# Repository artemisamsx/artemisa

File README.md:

# Artemisa MSX Computer System

This repository contains documentation and designs for a MSX computer that can be build using discrete components and original integrated circuits, codenamed Artemisa.

This is still work in progress, but you may find some specs and designs in this repository.

## Documentation

* [Artemisa User Manual](doc/user-manual/000-index.md).
* [Artemisa Service Manual](doc/service-manual/000-index.md).

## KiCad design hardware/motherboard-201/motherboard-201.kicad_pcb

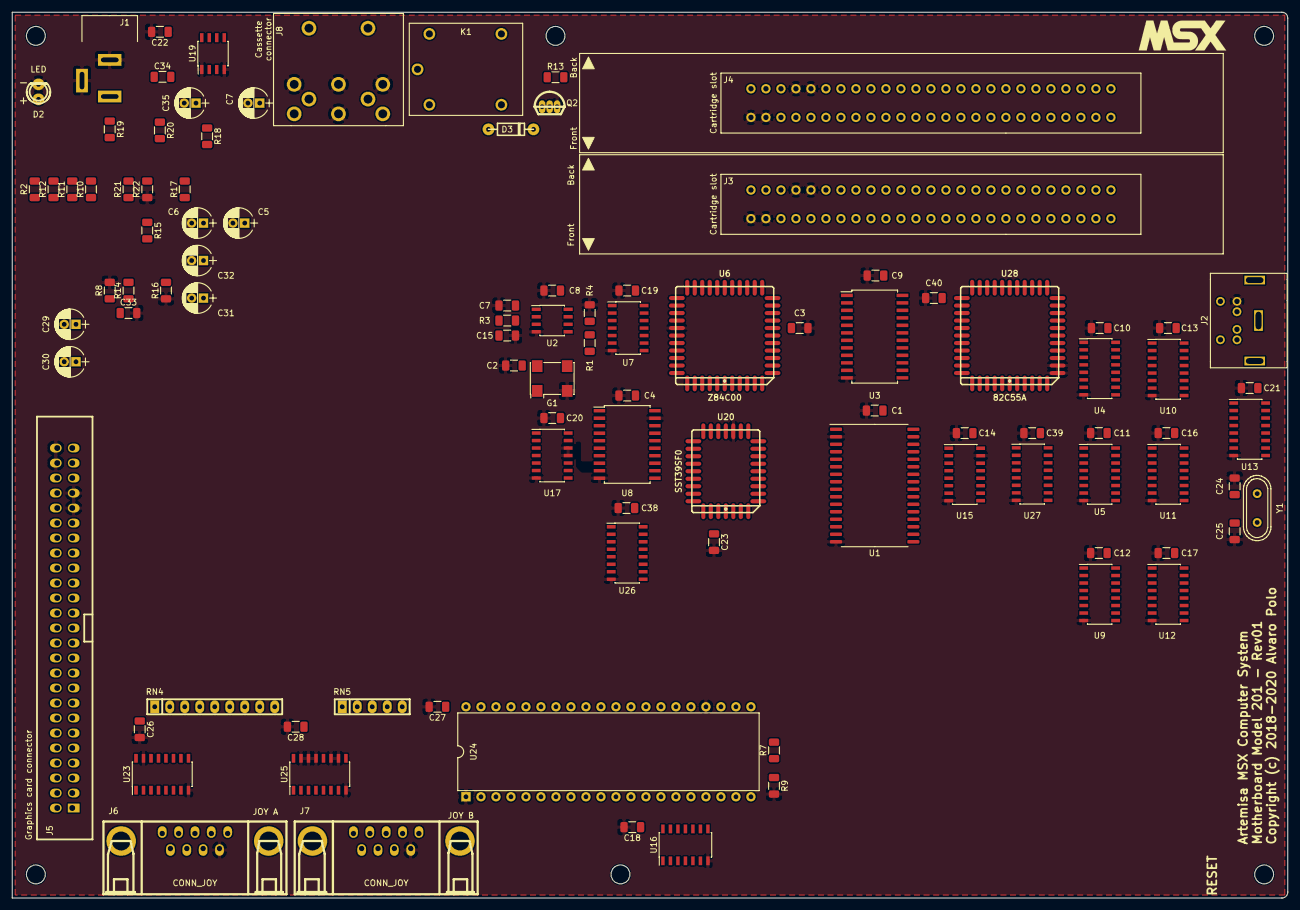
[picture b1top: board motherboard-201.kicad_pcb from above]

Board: 2 copper layers, 216.0 x 150.0 mm, 99 parts (0 on the bottom side), 158 nets, no tracks yet.

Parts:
C1, C2, C3, C4, C7, C8, C9, C14, C18, C19, C20, C22, C23, C26, C27, C28, C38, C39, C40: 100nF; C_1206
C5, C7#2: 100uF; Radial_capacitor
C6: 10uF; Radial_capacitor
C10, C11, C12, C13, C16, C17, C21: 0.1uF; C_1206
C15: 1uF; C_1206
C24, C25: 33pF; C_1206
C29, C30, C31: 10u; Radial_capacitor
C32, C35: 1uF; Radial_capacitor
C33, C34: 22nF; C_1206
D2: LED
D3: 1N4448; Axial_diode
G1: SG7050
J1: PWR_conn; Jack_55_21
J2: PS2_CONN; PS2_conn
J3, J4: MSX_Slot; Slot_conn
J5: GFX_Connector_Output; GFX_conn
J6, J7: CONN_JOY; Joystick_conn
J8: DIN8
K1: Relay
Q2: 2N2907; TO92
R1, R4, R7, R9: 10K; R_1206
R2: 220; R_1206
R3: 560; R_1206
R8: 470; R_1206
R10: 20k; R_1206
R11, R14, R15, R17: 4k7; R_1206
R12, R21, R22: 2k7; R_1206
R13: 2k2; R_1206
R16: 100; R_1206
R18: 220k; R_1206
R19: 1k; R_1206
R20: 10k; R_1206
RN4: 10K; RN8
RN5: 10K; RN4
U1: AS6C1008; SOP-32_450
U2: TL7705; SOIC-8_150
U3: GAL_declogic-201; SOIC-24
U4, U5, U9, U10, U11, U12: 74HC670; SOIC-16
U6: Z84C00; PLCC44
U7, U17: 74HC74; SOIC-14
U8: 74HCT245; SOIC-20
U13: ATMEGA328P; SOIC-16
U15: 74HC139; SOIC-16
U16: 74LS07; SOIC-14
U19: LM311; SOIC-8_150
U20: SST39SF0; PLCC32
U23, U25: 74HC157; SOIC-16
U24: AY-3-8910; DIP-40_600
U26: 74HC138; SOIC-16
U27: 74HC153; SOIC-16
U28: 82C55A; PLCC44
Y1: 16Mhz; Crystal

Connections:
/ADDR0: J3.28, J4.28, J5.28, U1.12, U3.9, U6.34, U20.12, U28.10
/ADDR1: J3.27, J4.27, J5.27, U1.11, U3.10, U6.35, U20.11, U28.9
/ADDR14: J3.25, J4.25, J5.25, U1.3, U3.11, U6.4, U20.29, U27.14
/ADDR15: J3.18, J4.18, J5.18, U1.31, U3.13, U6.5, U27.2
/AUDIO: J5.49, R10.2, R11.2, R12.2
/BEEP: C29.1, U28.11
/CASIN: R19.1, U19.7, U24.14
/CASOUT: C32.1, U28.14
/CLK: G1.3, J3.42, J4.42, J5.42, U6.7, U7.3, U7.11, U17.3
/CPU/ADDR2: J3.30, J4.30, J5.30, U1.10, U6.36, U20.10
/CPU/ADDR3: J3.29, J4.29, J5.29, U1.9, U6.37, U20.9, U26.1
/CPU/ADDR4: J3.32, J4.32, J5.32, U1.8, U6.38, U20.8, U26.2
/CPU/ADDR5: J3.31, J4.31, J5.31, U1.7, U6.39, U20.7, U26.3
/CPU/ADDR6: J3.22, J4.22, J5.22, U1.6, U6.40, U20.6, U26.5
/CPU/ADDR7: J3.21, J4.21, J5.21, U1.5, U6.41, U20.5, U26.6
/CPU/ADDR8: J3.24, J4.24, J5.24, U1.27, U6.42, U20.27
/CPU/ADDR9: J3.17, J4.17, J5.17, U1.26, U6.43, U20.26
/CPU/ADDR10: J3.20, J4.20, J5.20, U1.23, U6.44, U20.23
/CPU/ADDR11: J3.19, J4.19, J5.19, U1.25, U6.1, U20.25
/CPU/ADDR12: J3.23, J4.23, J5.23, U1.4, U6.2, U20.4
/CPU/ADDR13: J3.26, J4.26, J5.26, U1.28, U6.3, U20.28
/CPU/D0: U6.16, U8.2
/CPU/D1: U6.17, U8.3
/CPU/D2: U6.14, U8.4
/CPU/D3: U6.9, U8.5
/CPU/D4: U6.8, U8.6
/CPU/D5: U6.10, U8.7
/CPU/D6: U6.11, U8.8
/CPU/D7: U6.15, U8.9
/CPU/DATA0: J3.34, J4.34, J5.34, U1.13, U8.18, U20.13, U24.37, U28.38
/CPU/DATA1: J3.33, J4.33, J5.33, U1.14, U8.17, U20.14, U24.36, U28.37
/CPU/DATA2: J3.36, J4.36, J5.36, U1.15, U8.16, U20.15, U24.35, U28.36
/CPU/DATA3: J3.35, J4.35, J5.35, U1.17, U8.15, U20.17, U24.34, U28.35
/CPU/DATA4: J3.38, J4.38, J5.38, U1.18, U8.14, U20.18, U24.33, U28.33
/CPU/DATA5: J3.37, J4.37, J5.37, U1.19, U8.13, U20.19, U24.32, U28.32
/CPU/DATA6: J3.40, J4.40, J5.40, U1.20, U8.12, U20.20, U24.31, U28.31
/CPU/DATA7: J3.39, J4.39, J5.39, U1.21, U8.11, U20.21, U24.30, U28.30
/DATADIR: U3.14, U8.1
/DECODING/~IOSL: U3.20, U26.4
/DECODING/~PPISL: U3.7, U17.10, U26.10
/DECODING/~PSGSL: U3.8, U26.11
/EXTSOUND: C30.1, J3.49, J4.49
/KBD/D0: U4.15, U5.15, U9.15, U10.15, U11.15, U12.15
/KBD/D1: U4.1, U5.1, U9.1, U10.1, U11.1, U12.1
/KBD/D2: U4.2, U5.2, U9.2, U10.2, U11.2, U12.2
/KBD/D3: U4.3, U5.3, U9.3, U10.3, U11.3, U12.3
/KBD/KBCOL0: U4.10, U5.10, U9.10, U28.20
/KBD/KBCOL1: U4.9, U5.9, U9.9, U28.21
/KBD/KBCOL2: U4.7, U5.7, U9.7, U28.22
/KBD/KBCOL3: U4.6, U5.6, U9.6, U28.24
/KBD/KBCOL4: U10.10, U11.10, U12.10, U28.25
/KBD/KBCOL5: U10.9, U11.9, U12.9, U28.26
/KBD/KBCOL6: U10.7, U11.7, U12.7, U28.27
/KBD/KBCOL7: U10.6, U11.6, U12.6, U28.28
/KBD/KBROW0: U4.5, U5.5, U9.5, U10.5, U11.5, U12.5, U28.16
/KBD/KBROW1: U4.4, U5.4, U9.4, U10.4, U11.4, U12.4, U28.17
/KBD/KBROW2: U15.14, U28.18
/KBD/KBROW3: U15.13, U28.19
/KBD/ROW0: U4.14, U5.14, U9.14, U10.14, U11.14, U12.14
/KBD/ROW1: U4.13, U5.13, U9.13, U10.13, U11.13, U12.13
/KBD/~RSL0: U4.11, U10.11, U15.12
/KBD/~RSL1: U5.11, U11.11, U15.11
/KBD/~RSL2: U9.11, U12.11, U15.10
/KBD/~WSL0H: U10.12, U13.15
/KBD/~WSL0L: U4.12, U13.14
/KBD/~WSL1L: U5.12, U13.16
/PPI/PA0: U27.6, U28.5
/PPI/PA1: U27.10, U28.4
/PPI/PA2: U27.5, U28.3
/PPI/PA3: U27.11, U28.2
/PPI/PA4: U27.4, U28.44
/PPI/PA5: U27.12, U28.43
/PPI/PA6: U27.3, U28.42
/PPI/PA7: U27.13, U28.41
/PSG/IOA0: U23.4, U24.21
/PSG/IOA1: U23.7, U24.20
/PSG/IOA2: U23.9, U24.19
/PSG/IOA3: U23.12, U24.18
/PSG/IOA4: U24.17, U25.4
/PSG/IOA5: U24.16, U25.7
/PSG/IOB0: U16.1, U24.13
/PSG/IOB1: U16.3, U24.12
/PSG/IOB2: U16.5, U24.11
/PSG/IOB3: U16.9, U24.10
/PSG/IOB4: J6.8, U24.9
/PSG/IOB5: J7.8, U24.8
/PSG/IOB6: U23.1, U24.7, U25.1
/PSG/JOYA1: J6.1, RN4.9, U23.2
/PSG/JOYA2: J6.2, RN4.8, U23.5
/PSG/JOYA3: J6.3, RN4.7, U23.11
/PSG/JOYA4: J6.4, RN4.6, U23.14
/PSG/JOYA6: J6.6, RN5.5, U16.8, U25.2
/PSG/JOYA7: J6.7, RN5.4, U16.6, U25.5
/PSG/JOYB1: J7.1, RN4.5, U23.3
/PSG/JOYB2: J7.2, RN4.4, U23.6
/PSG/JOYB3: J7.3, RN4.3, U23.10
/PSG/JOYB4: J7.4, RN4.2, U23.13
/PSG/JOYB6: J7.6, RN5.3, U16.4, U25.3
/PSG/JOYB7: J7.7, RN5.2, U16.2, U25.6
/PSGBC1: U3.19, U24.29
/PSGBDIR: U3.18, U24.27
/PSGCLK: U17.5, U24.22
/RESET: R4.2, U2.6, U28.39
/~CAPSLOCK: U13.6, U28.13
/~CASMOTOR: R13.2, U28.15
/~CS1: J3.1, J4.1, J5.1, U3.21
/~CS2: J3.2, J4.2, J5.2, U3.22
/~CS12: J3.3, J4.3, J5.3, U3.23
/~INT: J3.8, J4.8, J5.8, U6.18
/~IORQ: J3.11, J4.11, J5.11, U3.4, U6.22
/~KANALOCK: R9.1, U13.11, U24.6
/~M1: J3.9, J4.9, J5.9, U3.5, U6.31, U7.2
/~MREQ: J3.12, J4.12, J5.12, U3.3, U6.21
/~PPIRD: U3.15, U28.6
/~PPIRDY: U17.8, U27.1, U27.15
/~PPIWR: U3.16, U28.40
/~RD: J3.14, J4.14, J5.14, U1.24, U3.1, U6.23, U20.24
/~RESET: J3.15, J4.15, J5.15, R1.2, U2.5, U6.30, U13.1, U17.13, U24.23
/~RFSH: J3.6, J4.6, J5.6, U3.6, U6.32
/~SLTSL0: U15.4, U20.22
/~SLTSL1: U1.22, U15.5
/~SLTSL2: J3.4, U15.6
/~SLTSL3: J4.4, U15.7
/~SLTSLEN: U3.17, U15.1
/~VDPSL: J5.16, U26.12
/~WAIT: J3.7, J4.7, J5.7, U7.1, U7.10
/~WR: J3.13, J4.13, J5.13, U1.29, U3.2, U6.26
GND: C1.2, C2.2, C3.2, C4.2, C5.2, C6.2, C7.2, C7#2.2, C8.1, C9.2, C10.1, C11.1, C12.1, C13.1, C14.2, C15.2, C16.1, C17.1, C18.2, C19.2, C20.2, C21.1, C22.2, C23.2, C24.1, C25.1, C26.2, C27.2, C28.2, C33.2, C35.2, C38.2, C39.2, C40.2, D2.2, G1.2, J1.2, J1.3, J2.3, J3.41, J3.43, J3.48, J3.50, J4.41, J4.43, J4.48, J4.50, J5.41, J5.43, J5.48, J5.50, J6.9, J7.9, J8.1, J8.2, J8.3, J8.8, Q2.1, R4.1, R8.2, R9.2, R16.1, R22.1, U1.2, U1.16, U2.4, U3.12, U4.8, U5.8, U6.33, U7.7, U8.10, U8.19, U9.8, U10.8, U11.8, U12.8, U13.8, U15.8, U15.15, U16.7, U17.7, U17.11, U17.12, U19.1, U19.4, U20.16, U23.8, U23.15, U24.1, U24.24, U25.8, U25.10, U25.11, U25.13, U25.14, U25.15, U26.8, U27.8, U28.7, U28.8
unnamed: C7.1, C7#2.1, U2.1
unnamed: C15.1, R3.2
unnamed: C24.2, U13.9, Y1.1
unnamed: C25.2, U13.10, Y1.2
unnamed: C29.2, R10.1
unnamed: C30.2, R11.1
unnamed: C31.1, R8.1, U24.3, U24.4, U24.38
unnamed: C31.2, R12.1
unnamed: C32.2, R14.2
unnamed: C33.1, R14.1, R15.2
unnamed: C34.1, R17.1
unnamed: C34.2, J8.5
unnamed: C35.1, R20.2, R21.1, R22.2, U19.2
unnamed: D2.1, R2.2
unnamed: D3.1, K1.2, Q2.3
unnamed: J2.1, U13.5
unnamed: J2.5, U13.4
unnamed: J8.4, R15.1, R16.2
unnamed: J8.6, K1.4
unnamed: J8.7, K1.3
unnamed: Q2.2, R13.1
unnamed: R3.1, U2.3
unnamed: R7.2, U24.15
unnamed: R17.2, R18.1, R20.1, U19.3
unnamed: U6.28, U7.5, U7.12
unnamed: U7.4, U7.9
unnamed: U15.2, U27.7
unnamed: U15.3, U27.9
unnamed: U17.2, U17.6
~: C1.1, C2.1, C3.1, C4.1, C5.1, C6.1, C8.2, C9.1, C10.2, C11.2, C12.2, C13.2, C14.1, C16.2, C17.2, C18.1, C19.1, C20.1, C21.2, C22.1, C23.1, C26.1, C27.1, C28.1, C38.1, C39.1, C40.1, D3.2, G1.1, G1.4, J1.1, J2.4, J3.45, J3.47, J4.45, J4.47, J5.4, J5.45, J5.47, J6.5, J7.5, K1.1, R1.1, R2.1, R7.1, R18.2, R19.2, R21.2, RN4.1, RN5.1, U1.30, U1.32, U2.2, U2.7, U2.8, U3.24, U4.16, U5.16, U6.13, U6.19, U6.29, U7.13, U7.14, U8.20, U9.16, U10.16, U11.16, U12.16, U13.7, U15.16, U16.14, U17.1, U17.4, U17.14, U19.8, U20.31, U20.32, U23.16, U24.25, U24.28, U24.40, U25.16, U26.16, U27.16, U28.29

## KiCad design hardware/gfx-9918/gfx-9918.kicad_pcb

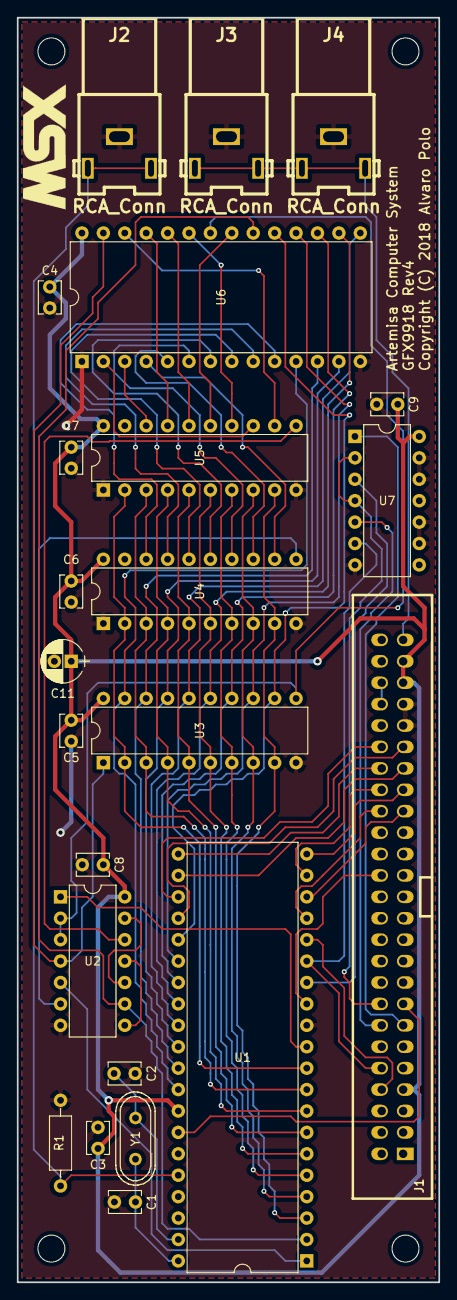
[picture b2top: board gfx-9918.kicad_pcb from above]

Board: 2 copper layers, 50.0 x 150.0 mm, 23 parts (0 on the bottom side), 62 nets.

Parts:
C1, C2: 56pF; Disc_capacitor
C3, C4, C5, C6, C7, C8, C9: 100nF; Disc_capacitor
C11: 10uF; Radial_capacitor
J1: GFX_Connector_Input; GFX_conn
J2: RCA_Conn; RCA_yellow
J3: RCA_Conn; RCA_white
J4: RCA_Conn; RCA_red
R1: 470; Axial_resistor
U1: TMS9918; DIP-40_600
U2: 74HCT04; DIP-14_300
U3, U4, U5: 74HCT574; DIP-20_300
U6: 62256; DIP-28_600
U7: 74HC32; DIP-14_300
Y1: 10.7386Mhz; Crystal

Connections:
/Input connector & power/A0: J1.28, U1.13
/Input connector & power/BUSDIR: J1.10, U1.15, U7.6
/Input connector & power/DATA0: J1.34, U1.17
/Input connector & power/DATA1: J1.33, U1.18
/Input connector & power/DATA2: J1.36, U1.19
/Input connector & power/DATA3: J1.35, U1.20
/Input connector & power/DATA4: J1.38, U1.21
/Input connector & power/DATA5: J1.37, U1.22
/Input connector & power/DATA6: J1.40, U1.23
/Input connector & power/DATA7: J1.39, U1.24
/Input connector & power/SOUNDOUT: J1.49, J3.1, J4.1
/Input connector & power/~INT: J1.8, U1.16
/Input connector & power/~RD: J1.14, U7.5
/Input connector & power/~RESET: J1.15, U1.34
/Input connector & power/~VDPIOSL: J1.16, U7.2, U7.4
/Input connector & power/~WR: J1.13, U7.1
/Interface Decoding Logic/~CSW: U1.14, U7.3
/Output connectors/CVBS: J2.1, R1.1, U1.36
/VRAM Decoding Logic/A0: U4.18, U6.10
/VRAM Decoding Logic/A1: U4.17, U6.9
/VRAM Decoding Logic/A2: U4.16, U6.8
/VRAM Decoding Logic/A3: U4.15, U6.7
/VRAM Decoding Logic/A4: U4.14, U6.6
/VRAM Decoding Logic/A5: U4.13, U6.5
/VRAM Decoding Logic/A6: U4.12, U6.4
/VRAM Decoding Logic/A7: U5.18, U6.3
/VRAM Decoding Logic/A8: U5.17, U6.25
/VRAM Decoding Logic/A9: U5.16, U6.24
/VRAM Decoding Logic/A10: U5.15, U6.21
/VRAM Decoding Logic/A11: U5.14, U6.23
/VRAM Decoding Logic/A12: U5.13, U6.2
/VRAM Decoding Logic/A13: U5.12, U6.26
/VRAM Decoding Logic/AD0: U1.10, U3.2, U4.2, U5.2
/VRAM Decoding Logic/AD1: U1.9, U3.3, U4.3, U5.3
/VRAM Decoding Logic/AD2: U1.8, U3.4, U4.4, U5.4
/VRAM Decoding Logic/AD3: U1.7, U3.5, U4.5, U5.5
/VRAM Decoding Logic/AD4: U1.6, U3.6, U4.6, U5.6
/VRAM Decoding Logic/AD5: U1.5, U3.7, U4.7, U5.7
/VRAM Decoding Logic/AD6: U1.4, U3.8, U4.8, U5.8
/VRAM Decoding Logic/AD7: U1.3, U3.9, U4.9, U5.9
/VRAM Decoding Logic/RD: U2.4, U3.1, U6.27
/VRAM Decoding Logic/WR: U2.2, U2.3, U3.11, U6.22
/VRAM Decoding Logic/~CAS: U1.2, U2.9, U6.20
/VRAM Decoding Logic/~RAS: U1.1, U2.5
/VRAM Decoding Logic/~WR: U1.11, U2.1
/VRAM/RD0: U1.32, U3.19, U6.11
/VRAM/RD1: U1.31, U3.18, U6.12
/VRAM/RD2: U1.30, U3.17, U6.13
/VRAM/RD3: U1.29, U3.16, U6.15
/VRAM/RD4: U1.28, U3.15, U6.16
/VRAM/RD5: U1.27, U3.14, U6.17
/VRAM/RD6: U1.26, U3.13, U6.18
/VRAM/RD7: U1.25, U3.12, U6.19
GND: C1.2, C2.2, C3.2, C4.2, C5.2, C6.2, C7.2, C8.2, C9.2, C11.2, J1.41, J1.43, J2.2, J3.2, J4.2, R1.2, U1.12, U2.7, U3.10, U4.1, U4.10, U5.1, U5.10, U6.1, U6.14, U7.7, U7.9, U7.10, U7.12, U7.13
unnamed: C1.1, U1.40, Y1.1
unnamed: C2.1, U1.39, Y1.2
unnamed: J1.44, J1.46
unnamed: U2.6, U4.11
unnamed: U2.10, U2.13
unnamed: U2.8, U2.11
unnamed: U2.12, U5.11
~: C3.1, C4.1, C5.1, C6.1, C7.1, C8.1, C9.1, C11.1, J1.7, J1.45, J1.47, U1.33, U2.14, U3.20, U4.20, U5.20, U6.28, U7.14

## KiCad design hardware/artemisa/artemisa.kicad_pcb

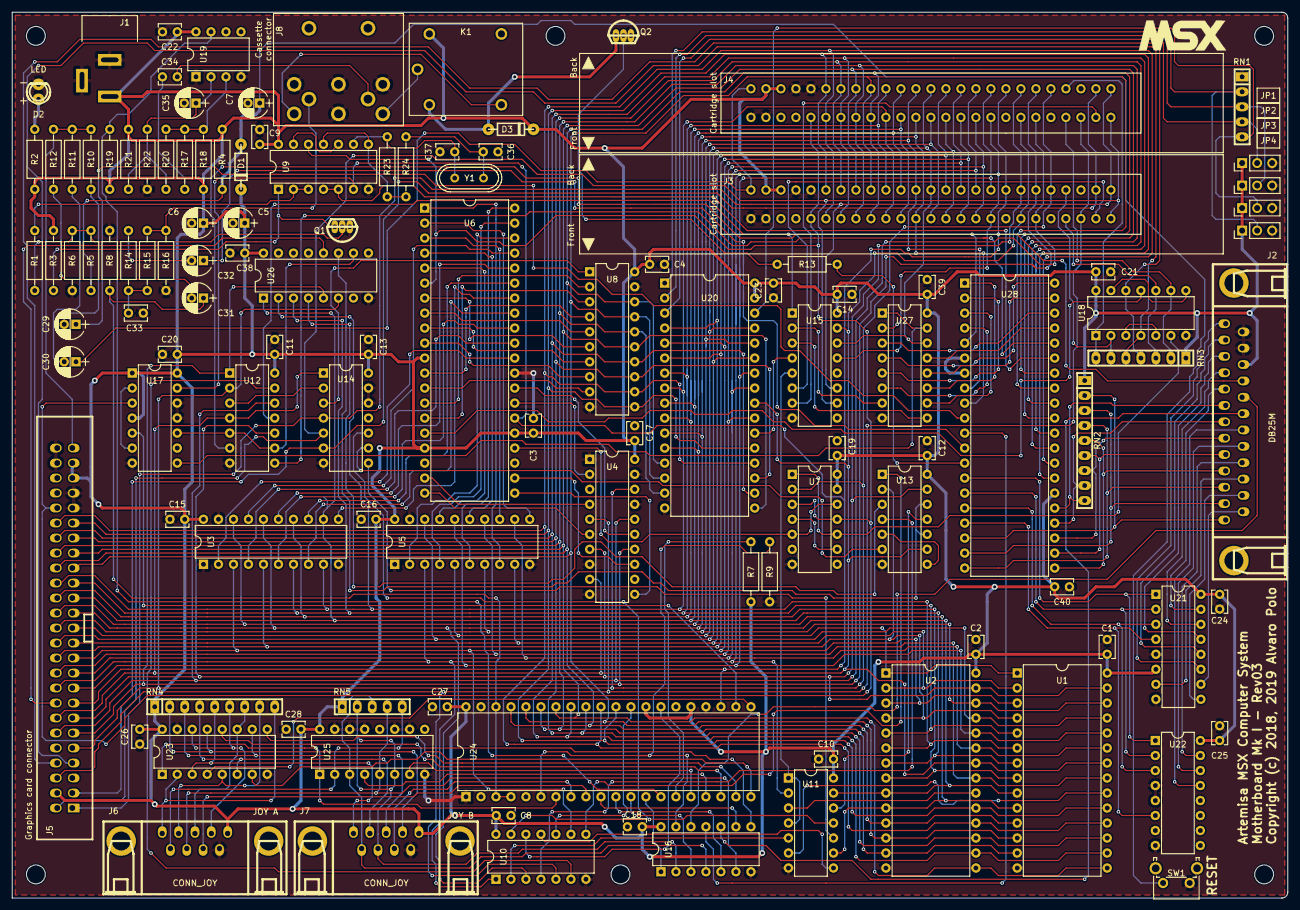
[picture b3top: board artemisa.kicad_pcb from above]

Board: 2 copper layers, 216.0 x 150.0 mm, 117 parts (0 on the bottom side), 207 nets.

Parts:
C1, C2, C3, C4, C8, C9, C10, C11, C12, C13, C14, C15, C16, C17, C18, C19, C20, C21, C22, C23, C24, C25, C26, C27, C28, C38, C39, C40: 100nF; Disc_capacitor
C5, C7: 100uF; Radial_capacitor
C6: 10uF; Radial_capacitor
C29, C30, C31: 10u; Radial_capacitor
C32, C35: 1uF; Radial_capacitor
C33, C34: 22nF; Disc_capacitor
C36, C37: 33pF; Disc_capacitor
D1, D3: 1N4448; Axial_diode
D2: LED
J1: PWR_conn; Jack_55_21
J2: DB25M
J3, J4: MSX_Slot; Slot_conn
J5: GFX_Connector_Output; GFX_conn
J6, J7: CONN_JOY; Joystick_conn
J8: DIN8
JP1, JP2, JP3, JP4: Jumper
K1: Relay
Q1: 2N2222; TO92
Q2: 2N2907; TO92
R1: 100K; Axial_resistor
R2: 220; Axial_resistor
R3, R6: 4K7; Axial_resistor
R4, R7, R9: 10K; Axial_resistor
R5, R24: 1K; Axial_resistor
R8: 470; Axial_resistor
R10: 20k; Axial_resistor
R11, R14, R15, R17: 4k7; Axial_resistor
R12, R21, R22: 2k7; Axial_resistor
R13: 2k2; Axial_resistor
R16: 100; Axial_resistor
R18: 220k; Axial_resistor
R19: 1k; Axial_resistor
R20: 10k; Axial_resistor
R23: 1M; Axial_resistor
RN1, RN5: 10K; RN4
RN2, RN4: 10K; RN8
RN3: 10K; RN6
SW1: Push_button; Push_button_angled
U1, U2: 62256; DIP-28_600
U3, U4, U5: 74HCT244; DIP-20_300
U6: Z84C00; DIP-40_600
U7, U17: 74HC74; DIP-14_300
U8: 74HCT245; DIP-20_300
U9: 74HCU04; DIP-14_300
U10: 74HC04; DIP-14_300
U11, U12, U13: 74HC32; DIP-14_300
U14: 74HC08; DIP-14_300
U15: 74HC139; DIP-16_300
U16: 74LS07; DIP-14_300
U18: 74HCT08; DIP-14_300
U19: LM311; DIP-8_300
U20: SST39SF0; DIP-32_600
U21, U22, U26: 74HC138; DIP-16_300
U23, U25: 74HC157; DIP-16_300
U24: AY-3-8910; DIP-40_600
U27: 74HC153; DIP-16_300
U28: 82C55A; DIP-40_600
Y1: 3.58Mhz; Crystal

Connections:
/ADDR0: J3.28, J4.28, J5.28, U1.10, U2.10, U3.18, U11.9, U20.12, U28.9
/ADDR1: J3.27, J4.27, J5.27, U1.9, U2.9, U3.16, U10.3, U11.13, U20.11, U28.8
/ADDR14: J3.25, J4.25, J5.25, U1.1, U2.1, U5.5, U15.14, U20.29, U27.14
/ADDR15: J3.18, J4.18, J5.18, U5.3, U10.1, U11.2, U15.13, U27.2
/AUDIO: J5.49, R10.2, R11.2, R12.2
/BEEP: C29.1, U28.10
/CASIN: R19.1, U19.7, U24.14
/CASOUT: C32.1, U28.12
/CLK: J3.42, J4.42, J5.42, U6.6, U7.3, U7.11, U9.12, U17.3
/CPU/A0: U3.2, U6.30
/CPU/A1: U3.4, U6.31
/CPU/A2: U3.6, U6.32
/CPU/A3: U3.8, U6.33
/CPU/A4: U3.11, U6.34
/CPU/A5: U3.13, U6.35
/CPU/A6: U3.15, U6.36
/CPU/A7: U3.17, U6.37
/CPU/A8: U5.2, U6.38
/CPU/A9: U5.4, U6.39
/CPU/A10: U5.6, U6.40
/CPU/A11: U5.8, U6.1
/CPU/A12: U5.11, U6.2
/CPU/A13: U5.13, U6.3
/CPU/A14: U5.15, U6.4
/CPU/A15: U5.17, U6.5
/CPU/ADDR2: J3.30, J4.30, J5.30, U1.8, U2.8, U3.14, U20.10
/CPU/ADDR3: J3.29, J4.29, J5.29, U1.7, U2.7, U3.12, U20.9, U26.1
/CPU/ADDR4: J3.32, J4.32, J5.32, U1.6, U2.6, U3.9, U20.8, U26.2
/CPU/ADDR5: J3.31, J4.31, J5.31, U1.5, U2.5, U3.7, U20.7, U26.3
/CPU/ADDR6: J3.22, J4.22, J5.22, U1.4, U2.4, U3.5, U13.2, U20.6
/CPU/ADDR7: J3.21, J4.21, J5.21, U1.3, U2.3, U3.3, U10.9, U20.5
/CPU/ADDR8: J3.24, J4.24, J5.24, U1.25, U2.25, U5.18, U20.27
/CPU/ADDR9: J3.17, J4.17, J5.17, U1.24, U2.24, U5.16, U20.26
/CPU/ADDR10: J3.20, J4.20, J5.20, U1.21, U2.21, U5.14, U20.23
/CPU/ADDR11: J3.19, J4.19, J5.19, U1.23, U2.23, U5.12, U20.25
/CPU/ADDR12: J3.23, J4.23, J5.23, U1.2, U2.2, U5.9, U20.4
/CPU/ADDR13: J3.26, J4.26, J5.26, U1.26, U2.26, U5.7, U20.28
/CPU/D0: U6.14, U8.2
/CPU/D1: U6.15, U8.3
/CPU/D2: U6.12, U8.4
/CPU/D3: U6.8, U8.5
/CPU/D4: U6.7, U8.6
/CPU/D5: U6.9, U8.7
/CPU/D6: U6.10, U8.8
/CPU/D7: U6.13, U8.9
/CPU/DATA0: J3.34, J4.34, J5.34, U1.11, U2.11, U8.18, U20.13, U24.37, U28.34
/CPU/DATA1: J3.33, J4.33, J5.33, U1.12, U2.12, U8.17, U20.14, U24.36, U28.33
/CPU/DATA2: J3.36, J4.36, J5.36, U1.13, U2.13, U8.16, U20.15, U24.35, U28.32
/CPU/DATA3: J3.35, J4.35, J5.35, U1.15, U2.15, U8.15, U20.17, U24.34, U28.31
/CPU/DATA4: J3.38, J4.38, J5.38, U1.16, U2.16, U8.14, U20.18, U24.33, U28.30
/CPU/DATA5: J3.37, J4.37, J5.37, U1.17, U2.17, U8.13, U20.19, U24.32, U28.29
/CPU/DATA6: J3.40, J4.40, J5.40, U1.18, U2.18, U8.12, U20.20, U24.31, U28.28
/CPU/DATA7: J3.39, J4.39, J5.39, U1.19, U2.19, U8.11, U20.21, U24.30, U28.27
/DATADIR: U8.1, U14.3
/DECODING/~PPISL: U12.5, U12.9, U17.10, U26.10
/DECODING/~PSGBDIR: U10.13, U11.11, U14.10
/DECODING/~PSGRD: U13.5, U13.8
/DECODING/~PSGSL: U13.10, U13.12, U26.11
/DECODING/~PSGWR: U11.12, U13.11
/EXTSOUND: C30.1, J3.49, J4.49
/KBD/KBCOL0: J2.1, RN2.2, U28.18
/KBD/KBCOL1: J2.2, RN2.3, U28.19
/KBD/KBCOL2: J2.3, RN2.4, U28.20
/KBD/KBCOL3: J2.4, RN2.5, U28.21
/KBD/KBCOL4: J2.5, RN2.6, U28.22
/KBD/KBCOL5: J2.6, RN2.7, U28.23
/KBD/KBCOL6: J2.7, RN2.8, U28.24
/KBD/KBCOL7: J2.8, RN2.9, U28.25
/KBD/KBROW0: U21.1, U22.1, U28.14
/KBD/KBROW1: U21.2, U22.2, U28.15
/KBD/KBROW2: U21.3, U22.3, U28.16
/KBD/KBROW3: U21.4, U22.6, U28.17
/KBD/~CAPSL: J2.20, U16.10
/KBD/~KANAL: J2.21, U16.12
/KBD/~RSL0: J2.9, U21.15
/KBD/~RSL1: J2.10, U21.14
/KBD/~RSL2: J2.11, U21.13
/KBD/~RSL3: J2.12, U21.12
/KBD/~RSL4: J2.13, U21.11
/KBD/~RSL5: J2.14, U21.10
/KBD/~RSL6: J2.15, U21.9
/KBD/~RSL7: J2.16, U21.7
/KBD/~RSL8: J2.17, U22.15
/KBD/~RSL9: J2.18, U22.14
/KBD/~RSL10: J2.19, U22.13
/PPI/PA0: U27.6, U28.4
/PPI/PA1: U27.10, U28.3
/PPI/PA2: U27.5, U28.2
/PPI/PA3: U27.11, U28.1
/PPI/PA4: U27.4, U28.40
/PPI/PA5: U27.12, U28.39
/PPI/PA6: U27.3, U28.38
/PPI/PA7: U27.13, U28.37
/PSG/IOA0: U23.4, U24.21
/PSG/IOA1: U23.7, U24.20
/PSG/IOA2: U23.9, U24.19
/PSG/IOA3: U23.12, U24.18
/PSG/IOA4: U24.17, U25.4
/PSG/IOA5: U24.16, U25.7
/PSG/IOB0: U16.1, U24.13
/PSG/IOB1: U16.3, U24.12
/PSG/IOB2: U16.5, U24.11
/PSG/IOB3: U16.9, U24.10
/PSG/IOB4: J6.8, U24.9
/PSG/IOB5: J7.8, U24.8
/PSG/IOB6: U23.1, U24.7, U25.1
/PSG/JOYA1: J6.1, RN4.9, U23.2
/PSG/JOYA2: J6.2, RN4.8, U23.5
/PSG/JOYA3: J6.3, RN4.7, U23.11
/PSG/JOYA4: J6.4, RN4.6, U23.14
/PSG/JOYA6: J6.6, RN5.5, U16.8, U25.2
/PSG/JOYA7: J6.7, RN5.4, U16.6, U25.5
/PSG/JOYB1: J7.1, RN4.5, U23.3
/PSG/JOYB2: J7.2, RN4.4, U23.6
/PSG/JOYB3: J7.3, RN4.3, U23.10
/PSG/JOYB4: J7.4, RN4.2, U23.13
/PSG/JOYB6: J7.6, RN5.3, U16.4, U25.3
/PSG/JOYB7: J7.7, RN5.2, U16.2, U25.6
/PSGBC1: U10.10, U24.29
/PSGBDIR: U10.12, U24.27
/PSGCLK: U17.5, U24.22
/RESET: U9.4, U9.5, U28.35
/SLOTS/~EXTINT2: J3.8, RN3.3, U18.10
/SLOTS/~EXTINT3: J4.8, RN3.2, U18.9
/SLOTS/~EXTWAIT2: J3.7, RN3.6, U18.2
/SLOTS/~EXTWAIT3: J4.7, RN3.7, U18.1
/SLOTS/~VDPINT: J5.8, RN3.4, U18.12
/SLOTS/~VDPWAIT: J5.7, RN3.5, U18.4
/~CAPSLOCK: U16.11, U28.11
/~CASMOTOR: R13.2, U28.13
/~CS1: J3.1, J4.1, J5.1, U14.4, U15.11
/~CS2: J3.2, J4.2, J5.2, U14.5, U15.10
/~CS12: J3.3, J4.3, J5.3, U14.6
/~EXTINT: U6.16, U18.11
/~EXTWAIT: U7.1, U7.10, U18.6
/~IORQ: J3.11, J4.11, J5.11, U4.14, U12.1, U26.5
/~KANALOCK: R9.1, U16.13, U24.6
/~M1: J3.9, J4.9, J5.9, U4.18, U7.2, U12.2, U26.6
/~MREQ: J3.12, J4.12, J5.12, U4.16, U12.12
/~PPIRD: U12.6, U28.5
/~PPIRDY: U17.8, U27.1, U27.15
/~PPIWR: U12.8, U28.36
/~RAMSL0: U1.20, U11.6
/~RAMSL1: U2.20, U11.3
/~RD: J3.14, J4.14, J5.14, U1.22, U2.22, U4.9, U12.4, U13.9, U14.1, U15.15, U20.24
/~RESET: J2.22, J3.15, J4.15, J5.15, U6.26, U9.6, U17.13, U24.23
/~RFSH: J3.6, J4.6, J5.6, U4.5, U10.5
/~SLTSL0: U15.4, U20.22
/~SLTSL1: U11.1, U11.4, U15.5
/~SLTSL2: J3.4, U15.6
/~SLTSL3: J4.4, U15.7
/~SLTSLEN: U12.11, U15.1
/~VDPSL: J5.16, U26.12
/~WR: J3.13, J4.13, J5.13, U1.27, U2.27, U4.7, U12.10, U13.13
GND: C1.2, C2.2, C3.2, C4.2, C5.2, C6.2, C7.2, C8.2, C9.2, C10.2, C11.2, C12.2, C13.2, C14.2, C15.2, C16.2, C17.2, C18.2, C19.2, C20.2, C21.2, C22.2, C23.2, C24.2, C25.2, C26.2, C27.2, C28.2, C33.2, C35.2, C36.2, C37.2, C38.2, C39.2, C40.2, D2.2, J1.2, J1.3, J2.24, J2.25, J3.41, J3.43, J3.48, J3.50, J4.41, J4.43, J4.48, J4.50, J5.41, J5.43, J5.48, J5.50, J6.9, J7.9, J8.1, J8.2, J8.3, J8.8, JP1.3, JP2.3, JP3.3, JP4.3, Q1.3, Q2.1, R6.2, R8.2, R9.2, R16.1, R22.1, RN1.1, SW1.1, U1.14, U2.14, U3.1, U3.10, U3.19, U4.1, U4.8, U4.10, U4.17, U4.19, U5.1, U5.10, U5.19, U6.29, U7.7, U8.10, U8.19, U9.7, U10.7, U11.7, U12.7, U13.7, U14.7, U14.12, U14.13, U15.8, U16.7, U17.7, U17.11, U17.12, U18.7, U19.1, U19.4, U20.16, U21.5, U21.8, U22.4, U22.5, U22.8, U23.8, U23.15, U24.1, U24.24, U25.8, U25.10, U25.11, U25.13, U25.14, U25.15, U26.8, U27.8, U28.6, U28.7
unnamed: C7.1, D1.1, R4.2, R5.2, SW1.2
unnamed: C29.2, R10.1
unnamed: C30.2, R11.1
unnamed: C31.1, R8.1, U24.3, U24.4, U24.38
unnamed: C31.2, R12.1
unnamed: C32.2, R14.2
unnamed: C33.1, R14.1, R15.2
unnamed: C34.1, R17.1
unnamed: C34.2, J8.5
unnamed: C35.1, R20.2, R21.1, R22.2, U19.2
unnamed: C36.1, R23.1, U9.9, Y1.1
unnamed: C37.1, R24.1, Y1.2
unnamed: D2.1, R2.2
unnamed: D3.1, K1.2, Q2.3
unnamed: J8.4, R15.1, R16.2
unnamed: J8.6, K1.4
unnamed: J8.7, K1.3
unnamed: JP1.2, RN1.4, U20.3
unnamed: JP2.2, RN1.3, U20.2
unnamed: JP3.2, RN1.5, U20.30
unnamed: JP4.2, RN1.2, U20.1
unnamed: Q1.1, R3.2, U9.1
unnamed: Q1.2, R1.2, R5.1, R6.1
unnamed: Q2.2, R13.1
unnamed: R1.1, U9.2, U9.3
unnamed: R7.2, U24.15
unnamed: R17.2, R18.1, R20.1, U19.3
unnamed: R23.2, R24.2, U9.8, U9.11
unnamed: U4.2, U6.27
unnamed: U4.4, U6.19
unnamed: U4.6, U6.20
unnamed: U4.11, U6.21
unnamed: U4.13, U6.22
unnamed: U4.15, U6.28
unnamed: U6.24, U7.5, U7.12
unnamed: U7.4, U7.9
unnamed: U9.10, U9.13
unnamed: U10.2, U11.5
unnamed: U10.4, U13.4
unnamed: U10.6, U12.13
unnamed: U10.8, U13.1
unnamed: U10.11, U11.8
unnamed: U11.10, U14.8
unnamed: U12.3, U14.2
unnamed: U13.3, U26.4
unnamed: U13.6, U14.9
unnamed: U15.2, U27.7
unnamed: U15.3, U27.9
unnamed: U17.2, U17.6
unnamed: U18.3, U18.5
unnamed: U18.8, U18.13
~: C1.1, C2.1, C3.1, C4.1, C5.1, C6.1, C8.1, C9.1, C10.1, C11.1, C12.1, C13.1, C14.1, C15.1, C16.1, C17.1, C18.1, C19.1, C20.1, C21.1, C22.1, C23.1, C24.1, C25.1, C26.1, C27.1, C28.1, C38.1, C39.1, C40.1, D1.2, D3.2, J1.1, J2.23, J3.45, J3.47, J4.45, J4.47, J5.4, J5.45, J5.47, J6.5, J7.5, JP1.1, JP2.1, JP3.1, JP4.1, K1.1, R2.1, R3.1, R4.1, R7.1, R18.2, R19.2, R21.2, RN2.1, RN3.1, RN4.1, RN5.1, U1.28, U2.28, U3.20, U4.20, U5.20, U6.11, U6.17, U6.25, U7.13, U7.14, U8.20, U9.14, U10.14, U11.14, U12.14, U13.14, U14.14, U15.16, U16.14, U17.1, U17.4, U17.14, U18.14, U19.8, U20.31, U20.32, U21.6, U21.16, U22.16, U23.16, U24.25, U24.28, U24.40, U25.16, U26.16, U27.16, U28.26

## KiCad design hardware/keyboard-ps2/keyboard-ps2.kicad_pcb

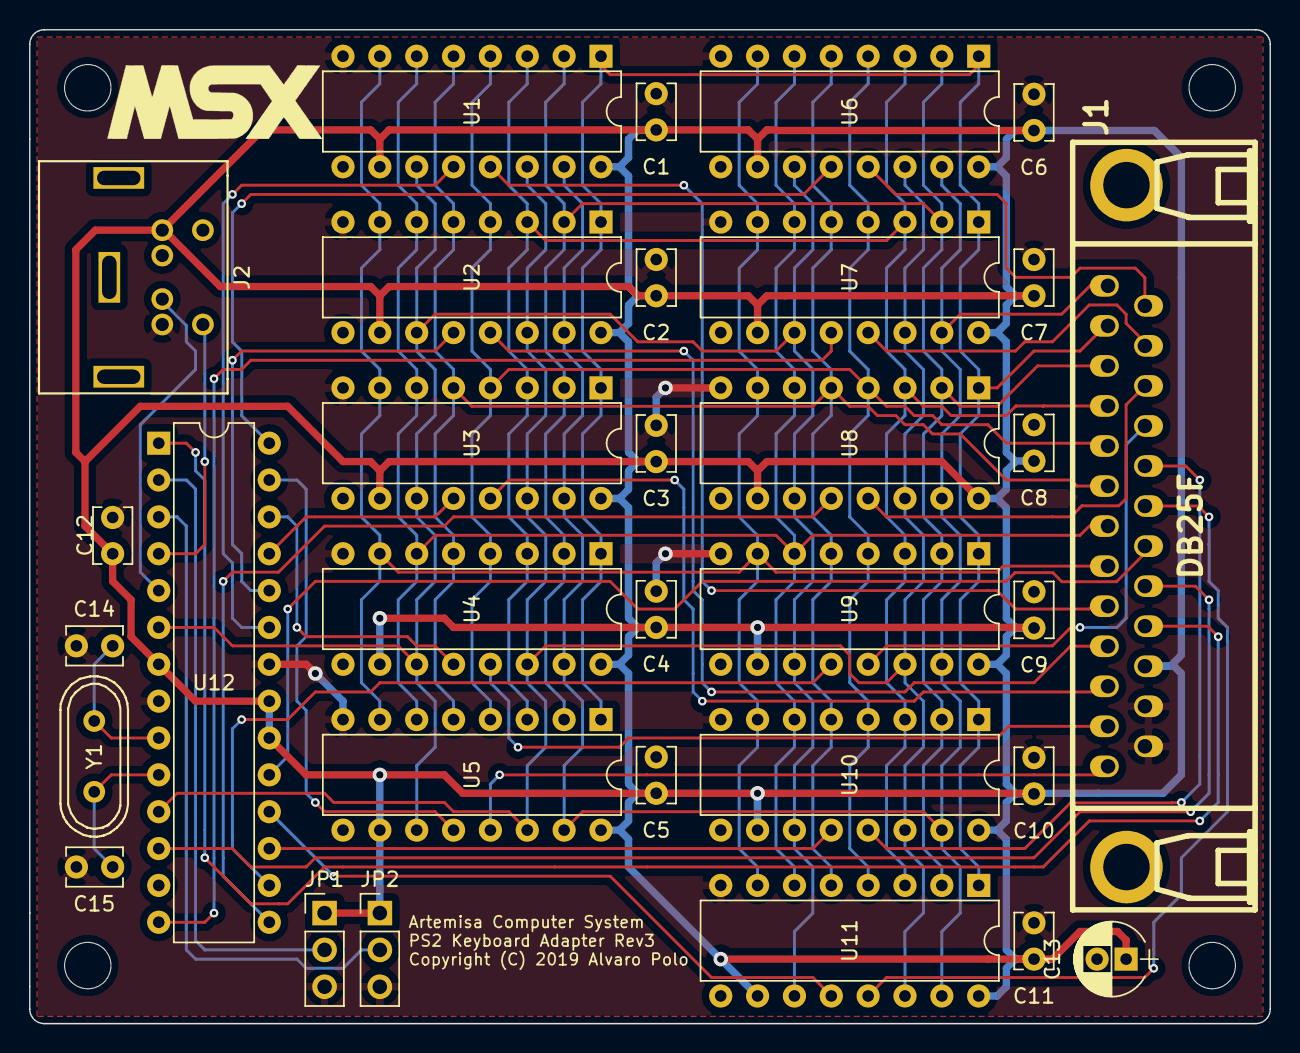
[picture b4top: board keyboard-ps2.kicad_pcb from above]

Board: 2 copper layers, 85.5 x 68.5 mm, 32 parts (0 on the bottom side), 43 nets.

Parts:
C1, C2, C3, C4, C5, C6, C7, C8, C9, C10, C11, C12: 100nF; Disc_capacitor
C13: 10uF; Radial_capacitor
C14, C15: 33pF; Disc_capacitor
J1: DB25F
J2: PS2_CONN; PS2_conn
JP1, JP2: Jumper
U1, U2, U3, U4, U5, U6, U7, U8, U9, U10, U11: 74HC595; DIP-16_300
U12: ATMEGA328P; DIP-28_300
Y1: 16Mhz; Crystal

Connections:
/DS: U1.14, U2.14, U3.14, U4.14, U5.14, U6.14, U7.14, U8.14, U9.14, U10.14, U11.14, U12.11
/KBCOL0: J1.1, U1.15, U2.15, U3.15, U4.15, U5.15, U6.15, U7.15, U8.15, U9.15, U10.15, U11.15
/KBCOL1: J1.2, U1.1, U2.1, U3.1, U4.1, U5.1, U6.1, U7.1, U8.1, U9.1, U10.1, U11.1
/KBCOL2: J1.3, U1.2, U2.2, U3.2, U4.2, U5.2, U6.2, U7.2, U8.2, U9.2, U10.2, U11.2
/KBCOL3: J1.4, U1.3, U2.3, U3.3, U4.3, U5.3, U6.3, U7.3, U8.3, U9.3, U10.3, U11.3
/KBCOL4: J1.5, U1.4, U2.4, U3.4, U4.4, U5.4, U6.4, U7.4, U8.4, U9.4, U10.4, U11.4
/KBCOL5: J1.6, U1.5, U2.5, U3.5, U4.5, U5.5, U6.5, U7.5, U8.5, U9.5, U10.5, U11.5
/KBCOL6: J1.7, U1.6, U2.6, U3.6, U4.6, U5.6, U6.6, U7.6, U8.6, U9.6, U10.6, U11.6
/KBCOL7: J1.8, U1.7, U2.7, U3.7, U4.7, U5.7, U6.7, U7.7, U8.7, U9.7, U10.7, U11.7
/SHCP: U1.11, U2.11, U3.11, U4.11, U5.11, U6.11, U7.11, U8.11, U9.11, U10.11, U11.11, U12.6
/STCP0: U1.12, U12.23
/STCP1: U2.12, U12.24
/STCP2: U3.12, U12.25
/STCP3: U4.12, U12.26
/STCP4: U5.12, U12.27
/STCP5: U6.12, U12.28
/STCP6: U7.12, U12.14
/STCP7: U8.12, U12.15
/STCP8: U9.12, U12.16
/STCP9: U10.12, U12.17
/STCP10: U11.12, U12.18
/~CAPSLOCK: J1.20, U12.19
/~KANALOCK: J1.21, U12.12
/~RESET: J1.22, U12.1
/~RSL0: J1.9, U1.13
/~RSL1: J1.10, U2.13
/~RSL2: J1.11, U3.13
/~RSL3: J1.12, U4.13
/~RSL4: J1.13, U5.13
/~RSL5: J1.14, U6.13
/~RSL6: J1.15, U7.13
/~RSL7: J1.16, U8.13
/~RSL8: J1.17, U9.13
/~RSL9: J1.18, U10.13
/~RSL10: J1.19, U11.13
GND: C1.2, C2.2, C3.2, C4.2, C5.2, C6.2, C7.2, C8.2, C9.2, C10.2, C11.2, C12.2, C13.2, C14.2, C15.2, J1.24, J1.25, J2.3, JP1.3, JP2.3, U1.8, U2.8, U3.8, U4.8, U5.8, U6.8, U7.8, U8.8, U9.8, U10.8, U11.8, U12.8, U12.22
unnamed: C14.1, U12.9, Y1.1
unnamed: C15.1, U12.10, Y1.2
unnamed: J2.1, U12.5
unnamed: J2.5, U12.4
unnamed: JP1.2, U12.2
unnamed: JP2.2, U12.3
~: C1.1, C2.1, C3.1, C4.1, C5.1, C6.1, C7.1, C8.1, C9.1, C10.1, C11.1, C12.1, C13.1, J1.23, J2.4, JP1.1, JP2.1, U1.10, U1.16, U2.10, U2.16, U3.10, U3.16, U4.10, U4.16, U5.10, U5.16, U6.10, U6.16, U7.10, U7.16, U8.10, U8.16, U9.10, U9.16, U10.10, U10.16, U11.10, U11.16, U12.7, U12.20, U12.21

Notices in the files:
hardware/gfx-9918/gfx-9918.kicad_pcb:
Copyright (C) 2018 Alvaro Polo
hardware/keyboard-ps2/keyboard-ps2.kicad_pcb:
Copyright (C) 2019 Alvaro Polo
hardware/motherboard-201/motherboard-201.kicad_pcb:
Copyright (c) 2018-2020 Alvaro Polo
